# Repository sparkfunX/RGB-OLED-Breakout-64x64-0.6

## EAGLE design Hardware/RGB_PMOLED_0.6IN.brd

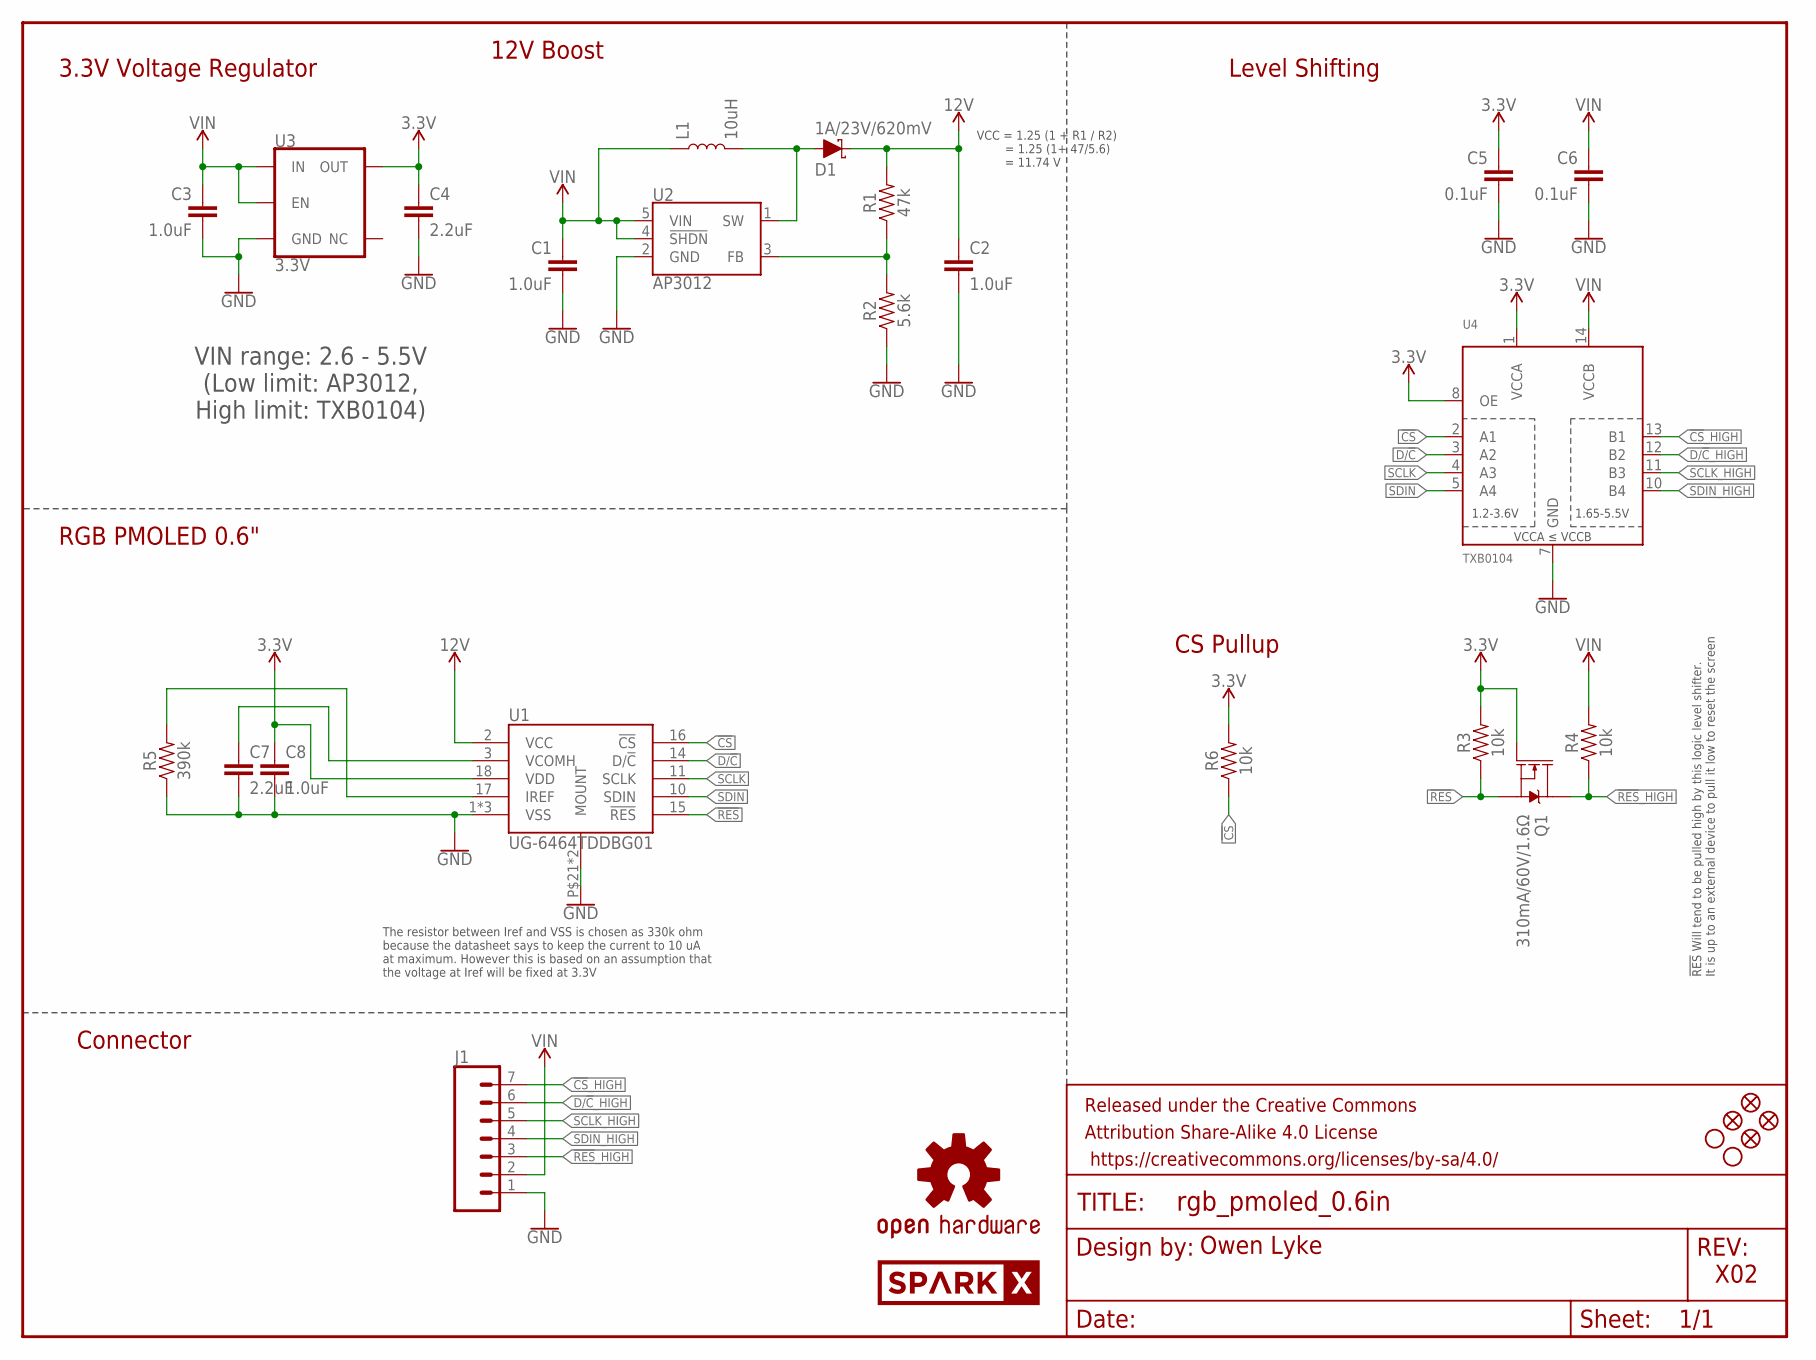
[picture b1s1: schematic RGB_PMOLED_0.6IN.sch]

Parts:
C1, C2, C3, C8: 1.0uF; 0603
C4: 2.2uF; 0603
C5, C6: 0.1uF; 0603
C7: 2.2uF; 0805
D1: 1A/23V/620mV; SOD-323
FD1, FD2, FD3, FD4: FIDUCIAL1X2; FIDUCIAL-1X2
FRAME1: FRAME-LETTER; CREATIVE_COMMONS
H1, H2: STAND-OFF
J1: CONN_07NO_SILK; 1X07_NO_SILK
L1: 10uH; INDUCTOR_4.7UH
LOGO1: SPARKX-LOGO5; SPARKX-LARGE
LOGO2: OSHW-LOGOS; OSHW-LOGO-S
Q1: 310mA/60V/1.6Ω; SOT323
R1: 47k; 0603
R2: 5.6k; 0603
R3, R4, R6: 10k; 0603
R5: 390k; 0603
U1: UG-6464TDDBG01; AMPHENOL_10051922-2010ELF
U2: AP3012; SOT23-5
U3: 3.3V; SOT23-5
U4: TXB0104; SO14

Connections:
3.3V: C4.1, C5.1, C8.1, Q1.1 (G), R3.2, R6.2, U1.18 (VDD), U3.5 (OUT), U4.1 (VCCA), U4.8 (OE)
12V: C2.1, D1.C, R1.2, U1.2 (VCC)
!CS: R6.1, U1.16 (!CS), U4.2 (A1)
!CS!_HIGH: J1.7, U4.13 (B1)
!RES: Q1.2 (S), R3.1, U1.15 (!RES)
!RES!_HIGH: J1.3, Q1.3 (D), R4.1
D/!C: U1.14 (D/!C), U4.3 (A2)
D/!C!_HIGH: J1.6, U4.12 (B2)
GND: C1.2, C2.2, C3.2, C4.2, C5.2, C6.2, C7.2, C8.2, J1.1, R2.1, R5.1, U1.1 (VSS), U1.19 (VSS), U1.20 (VSS), U1.P$21 (MOUNT), U1.P$22 (MOUNT), U2.2 (GND), U3.2 (GND), U4.7 (GND)
unnamed: D1.A, L1.P$2 (2), U2.1 (SW)
unnamed: R1.1, R2.2, U2.3 (FB)
unnamed: C7.1, U1.3 (VCOMH)
unnamed: R5.2, U1.17 (IREF)
SCLK: U1.11 (SCLK), U4.4 (A3)
SCLK_HIGH: J1.5, U4.11 (B3)
SDIN: U1.10 (SDIN), U4.5 (A4)
SDIN_HIGH: J1.4, U4.10 (B4)
VIN: C1.1, C3.1, C6.1, J1.2, L1.P$1 (1), R4.2, U2.4 (!SHDN!), U2.5 (VIN), U3.1 (IN), U3.3 (EN), U4.14 (VCCB)

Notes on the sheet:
VCC = 1.25 (1 + R1 / R2) = 1.25 (1+ 47/5.6) = 11.74 V
12V Boost
VIN range: 2.6 - 5.5V (Low limit: AP3012, High limit: TXB0104)
3.3V Voltage Regulator
Level Shifting
Owen Lyke
!RES! Will tend to be pulled high by this logic level shifter. It is up to an external device to pull it low to reset the screen
The resistor between Iref and VSS is chosen as 330k ohm because the datasheet says to keep the current to 10 uA at maximum. However this is based on an assumption that the voltage at Iref will be fixed at 3.3V
RGB PMOLED 0.6"
Connector
X02
CS Pullup

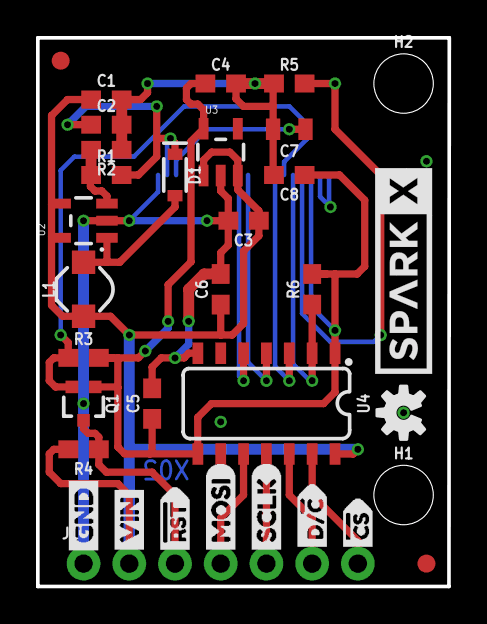
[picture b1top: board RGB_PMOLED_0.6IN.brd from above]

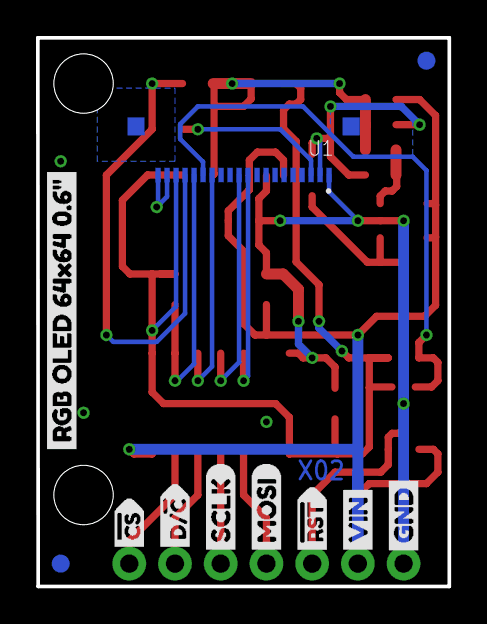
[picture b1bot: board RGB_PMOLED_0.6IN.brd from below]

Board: 2 copper layers, 22.9 x 30.5 mm, 46 parts (11 on the bottom side), 18 nets.

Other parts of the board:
U$1, U$2: VIN0
U$3, U$4: MOSI1
U$5, U$6: SCLK2
U$7, U$8: GND1
U$9, U$14: D##C5
U$10, U$11: #RST0
U$12, U$13: #CS6
U$16: RGB_OLED_64X64_0#6#7

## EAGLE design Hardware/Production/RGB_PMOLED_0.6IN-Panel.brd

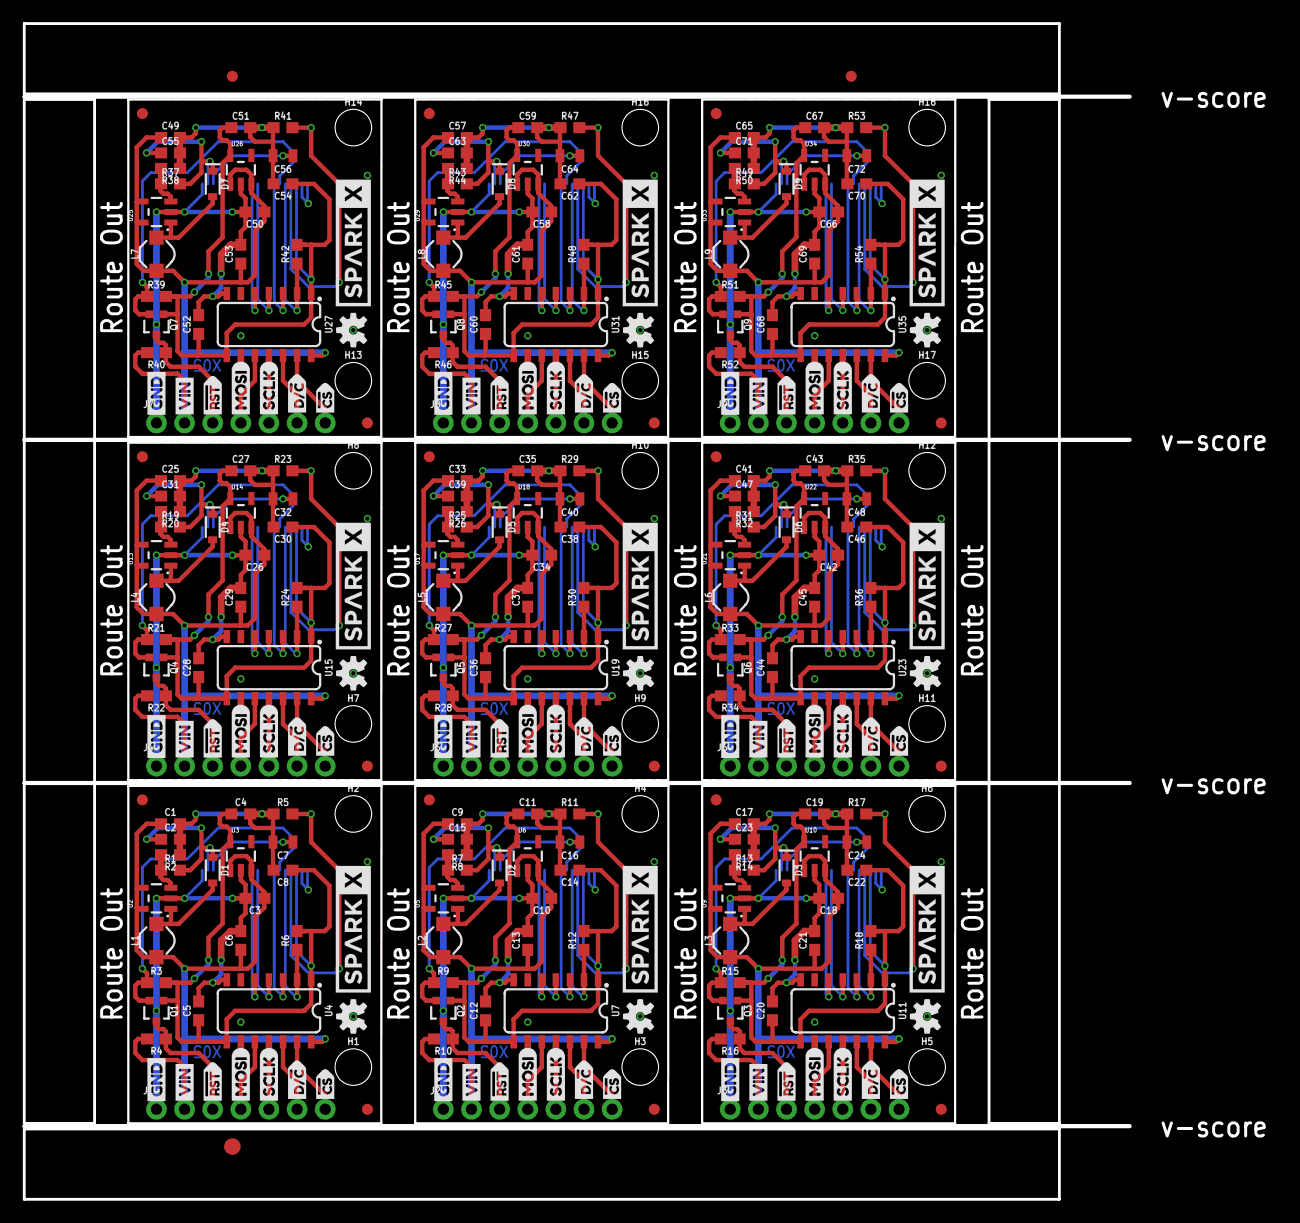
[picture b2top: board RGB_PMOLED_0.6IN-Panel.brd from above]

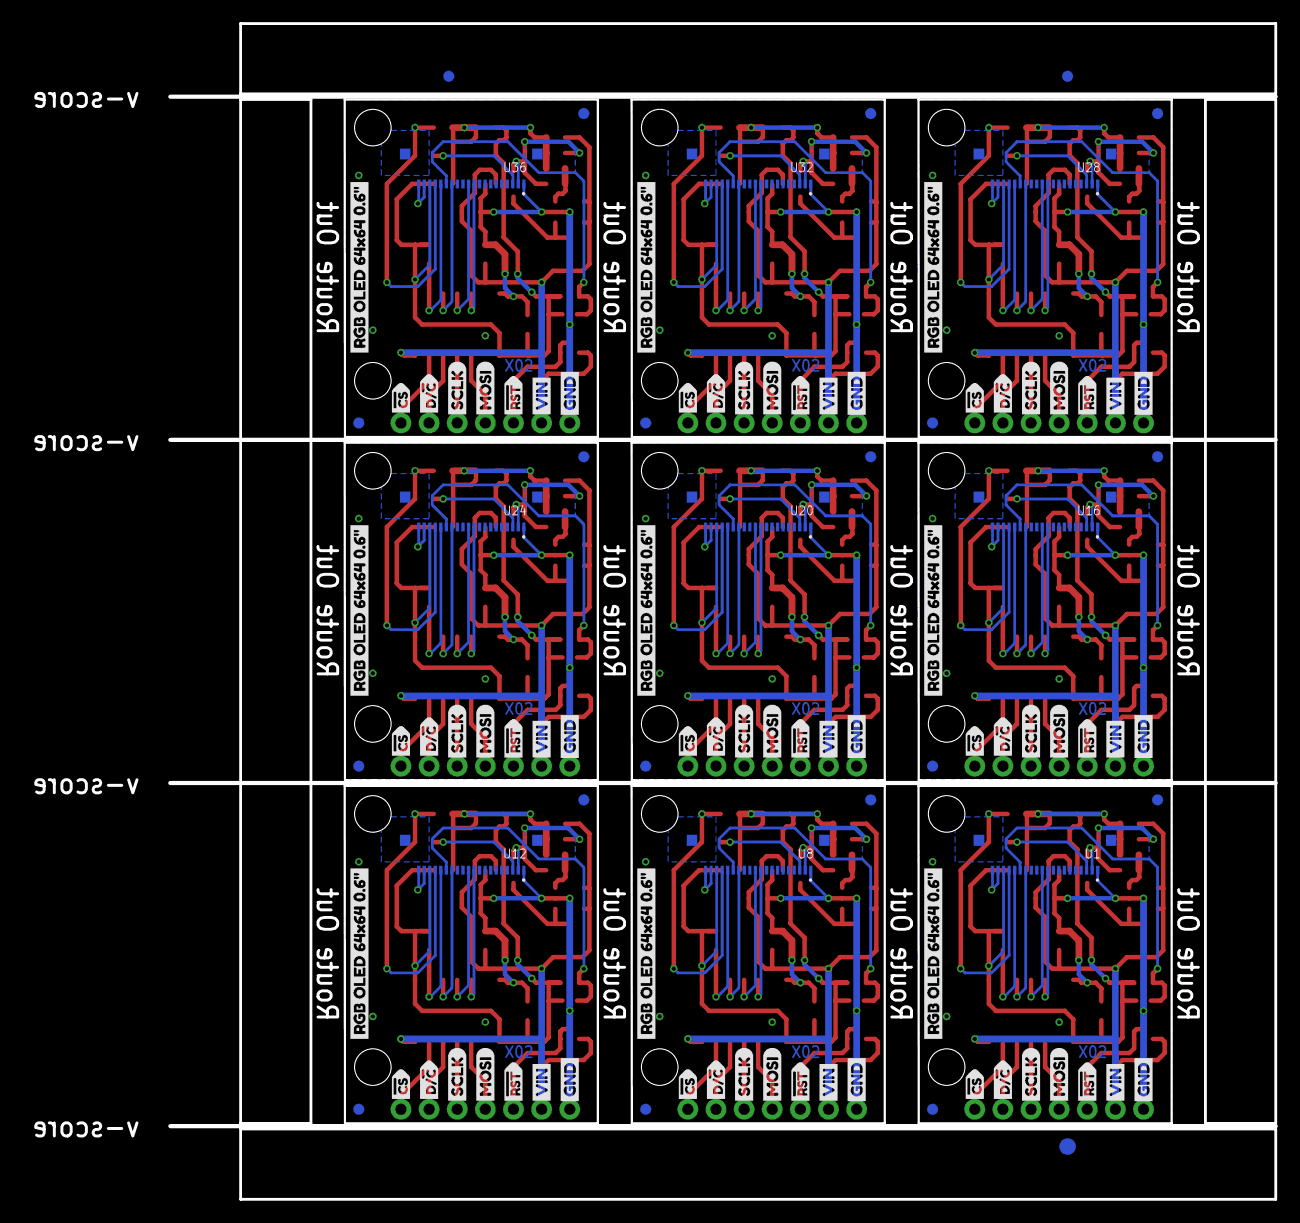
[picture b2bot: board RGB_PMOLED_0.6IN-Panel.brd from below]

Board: 2 copper layers, 113.0 x 106.0 mm, 411 parts (102 on the bottom side), 162 nets.

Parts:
C1, C2, C3, C8, C9, C10, C14, C15, C17, C18, C22, C23, C25, C26, C30, C31, C33, C34, C38, C39, C41, C42, C46, C47, C49, C50, C54, C55, C57, C58, C62, C63, C65, C66, C70, C71: 1.0uF; 0603
C4, C11, C19, C27, C35, C43, C51, C59, C67: 2.2uF; 0603
C5, C6, C12, C13, C20, C21, C28, C29, C36, C37, C44, C45, C52, C53, C60, C61, C68, C69: 0.1uF; 0603
C7, C16, C24, C32, C40, C48, C56, C64, C72: 2.2uF; 0805
D1, D2, D3, D4, D5, D6, D7, D8, D9: 1A/23V/620mV; SOD-323
E$1, E$2, E$3, E$4: FIDUCIAL-1X2
E$5, E$6: FIDUCIAL-1.5X3
FD1, FD2, FD3, FD4, FD5, FD6, FD7, FD8, FD9, FD10, FD11, FD12, FD13, FD14, FD15, FD16, FD17, FD18, FD19, FD20, FD21, FD22, FD23, FD24, FD25, FD26, FD27, FD28, FD29, FD30, FD31, FD32, FD33, FD34, FD35, FD36: FIDUCIAL1X2; FIDUCIAL-1X2
H1, H2, H3, H4, H5, H6, H7, H8, H9, H10, H11, H12, H13, H14, H15, H16, H17, H18: STAND-OFF
J1, J2, J3, J4, J5, J6, J7, J8, J9: 1X07_NO_SILK
L1, L2, L3, L4, L5, L6, L7, L8, L9: 10uH; INDUCTOR_4.7UH
LOGO1, LOGO3, LOGO5, LOGO7, LOGO9, LOGO11, LOGO13, LOGO15, LOGO17: SPARKX-LOGO5; SPARKX-LARGE
LOGO2, LOGO4, LOGO6, LOGO8, LOGO10, LOGO12, LOGO14, LOGO16, LOGO18: OSHW-LOGOS; OSHW-LOGO-S
Q1, Q2, Q3, Q4, Q5, Q6, Q7, Q8, Q9: 310mA/60V/1.6Ω; SOT323
R1, R7, R13, R19, R25, R31, R37, R43, R49: 47k; 0603
R2, R8, R14, R20, R26, R32, R38, R44, R50: 5.6k; 0603
R3, R4, R6, R9, R10, R12, R15, R16, R18, R21, R22, R24, R27, R28, R30, R33, R34, R36, R39, R40, R42, R45, R46, R48, R51, R52, R54: 10k; 0603
R5, R11, R17, R23, R29, R35, R41, R47, R53: 390k; 0603
U1, U8, U12, U16, U20, U24, U28, U32, U36: UG-6464TDDBG01; AMPHENOL_10051922-2010ELF
U2, U5, U9, U13, U17, U21, U25, U29, U33: AP3012; SOT23-5
U3, U6, U10, U14, U18, U22, U26, U30, U34: 3.3V; SOT23-5
U4, U7, U11, U15, U19, U23, U27, U31, U35: TXB0104; SO14
U$1, U$2, U$15, U$17, U$31, U$32, U$46, U$47, U$61, U$62, U$76, U$77, U$91, U$92, U$106, U$107, U$121, U$122: VIN0
U$3, U$4, U$27, U$28, U$42, U$43, U$57, U$58, U$72, U$73, U$87, U$88, U$102, U$103, U$117, U$118, U$132, U$133: MOSI1
U$5, U$6, U$29, U$30, U$44, U$45, U$59, U$60, U$74, U$75, U$89, U$90, U$104, U$105, U$119, U$120, U$134, U$135: SCLK2
U$7, U$8, U$18, U$19, U$33, U$34, U$48, U$49, U$63, U$64, U$78, U$79, U$93, U$94, U$108, U$109, U$123, U$124: GND1
U$9, U$14, U$22, U$23, U$37, U$38, U$52, U$53, U$67, U$68, U$82, U$83, U$97, U$98, U$112, U$113, U$127, U$128: D##C5
U$10, U$11, U$25, U$26, U$40, U$41, U$55, U$56, U$70, U$71, U$85, U$86, U$100, U$101, U$115, U$116, U$130, U$131: #RST0
U$12, U$13, U$20, U$21, U$35, U$36, U$50, U$51, U$65, U$66, U$80, U$81, U$95, U$96, U$110, U$111, U$125, U$126: #CS6
U$16, U$24, U$39, U$54, U$69, U$84, U$99, U$114, U$129: RGB_OLED_64X64_0#6#7

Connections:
3.3V: C4.1, C5.1, C8.1, Q1.1, R3.2, R6.2, U1.18, U3.5, U4.1, U4.8
3.3V1: C11.1, C12.1, C14.1, Q2.1, R9.2, R12.2, U6.5, U7.1, U7.8, U8.18
3.3V2: C19.1, C20.1, C22.1, Q3.1, R15.2, R18.2, U10.5, U11.1, U11.8, U12.18
3.3V3: C27.1, C28.1, C30.1, Q4.1, R21.2, R24.2, U14.5, U15.1, U15.8, U16.18
3.3V4: C35.1, C36.1, C38.1, Q5.1, R27.2, R30.2, U18.5, U19.1, U19.8, U20.18
3.3V5: C43.1, C44.1, C46.1, Q6.1, R33.2, R36.2, U22.5, U23.1, U23.8, U24.18
3.3V6: C51.1, C52.1, C54.1, Q7.1, R39.2, R42.2, U26.5, U27.1, U27.8, U28.18
3.3V7: C59.1, C60.1, C62.1, Q8.1, R45.2, R48.2, U30.5, U31.1, U31.8, U32.18
3.3V8: C67.1, C68.1, C70.1, Q9.1, R51.2, R54.2, U34.5, U35.1, U35.8, U36.18
12V: C2.1, D1.C, R1.2, U1.2
12V1: C15.1, D2.C, R7.2, U8.2
12V2: C23.1, D3.C, R13.2, U12.2
12V3: C31.1, D4.C, R19.2, U16.2
12V4: C39.1, D5.C, R25.2, U20.2
12V5: C47.1, D6.C, R31.2, U24.2
12V6: C55.1, D7.C, R37.2, U28.2
12V7: C63.1, D8.C, R43.2, U32.2
12V8: C71.1, D9.C, R49.2, U36.2
!CS: R6.1, U1.16, U4.2
!CS1: R12.1, U7.2, U8.16
!CS2: R18.1, U11.2, U12.16
!CS3: R24.1, U15.2, U16.16
!CS4: R30.1, U19.2, U20.16
!CS5: R36.1, U23.2, U24.16
!CS6: R42.1, U27.2, U28.16
!CS7: R48.1, U31.2, U32.16
!CS8: R54.1, U35.2, U36.16
!CS!_HIGH: J1.7, U4.13
!CS!_HIGH1: J2.7, U7.13
!CS!_HIGH2: J3.7, U11.13
!CS!_HIGH3: J4.7, U15.13
!CS!_HIGH4: J5.7, U19.13
!CS!_HIGH5: J6.7, U23.13
!CS!_HIGH6: J7.7, U27.13
!CS!_HIGH7: J8.7, U31.13
!CS!_HIGH8: J9.7, U35.13
!RES: Q1.2, R3.1, U1.15
!RES1: Q2.2, R9.1, U8.15
!RES2: Q3.2, R15.1, U12.15
!RES3: Q4.2, R21.1, U16.15
!RES4: Q5.2, R27.1, U20.15
!RES5: Q6.2, R33.1, U24.15
!RES6: Q7.2, R39.1, U28.15
!RES7: Q8.2, R45.1, U32.15
!RES8: Q9.2, R51.1, U36.15
!RES!_HIGH: J1.3, Q1.3, R4.1
!RES!_HIGH1: J2.3, Q2.3, R10.1
!RES!_HIGH2: J3.3, Q3.3, R16.1
!RES!_HIGH3: J4.3, Q4.3, R22.1
!RES!_HIGH4: J5.3, Q5.3, R28.1
!RES!_HIGH5: J6.3, Q6.3, R34.1
!RES!_HIGH6: J7.3, Q7.3, R40.1
!RES!_HIGH7: J8.3, Q8.3, R46.1
!RES!_HIGH8: J9.3, Q9.3, R52.1
D/!C: U1.14, U4.3
D/!C1: U7.3, U8.14
D/!C2: U11.3, U12.14
D/!C3: U15.3, U16.14
D/!C4: U19.3, U20.14
D/!C5: U23.3, U24.14
D/!C6: U27.3, U28.14
D/!C7: U31.3, U32.14
D/!C8: U35.3, U36.14
D/!C!_HIGH: J1.6, U4.12
D/!C!_HIGH1: J2.6, U7.12
D/!C!_HIGH2: J3.6, U11.12
D/!C!_HIGH3: J4.6, U15.12
D/!C!_HIGH4: J5.6, U19.12
D/!C!_HIGH5: J6.6, U23.12
D/!C!_HIGH6: J7.6, U27.12
D/!C!_HIGH7: J8.6, U31.12
D/!C!_HIGH8: J9.6, U35.12
GND: C1.2, C2.2, C3.2, C4.2, C5.2, C6.2, C7.2, C8.2, J1.1, R2.1, R5.1, U1.1, U1.19, U1.20, U1.P$21, U1.P$22, U2.2, U3.2, U4.7
GND1: C9.2, C10.2, C11.2, C12.2, C13.2, C14.2, C15.2, C16.2, J2.1, R8.1, R11.1, U5.2, U6.2, U7.7, U8.1, U8.19, U8.20, U8.P$21, U8.P$22
GND2: C17.2, C18.2, C19.2, C20.2, C21.2, C22.2, C23.2, C24.2, J3.1, R14.1, R17.1, U9.2, U10.2, U11.7, U12.1, U12.19, U12.20, U12.P$21, U12.P$22
GND3: C25.2, C26.2, C27.2, C28.2, C29.2, C30.2, C31.2, C32.2, J4.1, R20.1, R23.1, U13.2, U14.2, U15.7, U16.1, U16.19, U16.20, U16.P$21, U16.P$22
GND4: C33.2, C34.2, C35.2, C36.2, C37.2, C38.2, C39.2, C40.2, J5.1, R26.1, R29.1, U17.2, U18.2, U19.7, U20.1, U20.19, U20.20, U20.P$21, U20.P$22
GND5: C41.2, C42.2, C43.2, C44.2, C45.2, C46.2, C47.2, C48.2, J6.1, R32.1, R35.1, U21.2, U22.2, U23.7, U24.1, U24.19, U24.20, U24.P$21, U24.P$22
GND6: C49.2, C50.2, C51.2, C52.2, C53.2, C54.2, C55.2, C56.2, J7.1, R38.1, R41.1, U25.2, U26.2, U27.7, U28.1, U28.19, U28.20, U28.P$21, U28.P$22
GND7: C57.2, C58.2, C59.2, C60.2, C61.2, C62.2, C63.2, C64.2, J8.1, R44.1, R47.1, U29.2, U30.2, U31.7, U32.1, U32.19, U32.20, U32.P$21, U32.P$22
GND8: C65.2, C66.2, C67.2, C68.2, C69.2, C70.2, C71.2, C72.2, J9.1, R50.1, R53.1, U33.2, U34.2, U35.7, U36.1, U36.19, U36.20, U36.P$21, U36.P$22
unnamed: D2.A, L2.P$2, U5.1
unnamed: D1.A, L1.P$2, U2.1
unnamed: R1.1, R2.2, U2.3
unnamed: R7.1, R8.2, U5.3
unnamed: C7.1, U1.3
unnamed: R11.2, U8.17
unnamed: C16.1, U8.3
unnamed: D3.A, L3.P$2, U9.1
unnamed: R13.1, R14.2, U9.3
unnamed: R17.2, U12.17
unnamed: R5.2, U1.17
unnamed: C24.1, U12.3
unnamed: D4.A, L4.P$2, U13.1
unnamed: R19.1, R20.2, U13.3
unnamed: R23.2, U16.17
unnamed: C32.1, U16.3
unnamed: D5.A, L5.P$2, U17.1
unnamed: R25.1, R26.2, U17.3
unnamed: R29.2, U20.17
unnamed: C40.1, U20.3
unnamed: D6.A, L6.P$2, U21.1
unnamed: R31.1, R32.2, U21.3
unnamed: R35.2, U24.17
unnamed: C48.1, U24.3
unnamed: D7.A, L7.P$2, U25.1
unnamed: R37.1, R38.2, U25.3
unnamed: R41.2, U28.17
unnamed: C56.1, U28.3
unnamed: D8.A, L8.P$2, U29.1
unnamed: R43.1, R44.2, U29.3
unnamed: R47.2, U32.17
unnamed: C64.1, U32.3
unnamed: D9.A, L9.P$2, U33.1
unnamed: R49.1, R50.2, U33.3
unnamed: R53.2, U36.17
unnamed: C72.1, U36.3
SCLK: U1.11, U4.4
SCLK1: U7.4, U8.11
SCLK2: U11.4, U12.11
SCLK3: U15.4, U16.11
SCLK4: U19.4, U20.11
SCLK5: U23.4, U24.11
SCLK6: U27.4, U28.11
SCLK7: U31.4, U32.11
SCLK8: U35.4, U36.11
SCLK_HIGH: J1.5, U4.11
SCLK_HIGH1: J2.5, U7.11
SCLK_HIGH2: J3.5, U11.11
SCLK_HIGH3: J4.5, U15.11
SCLK_HIGH4: J5.5, U19.11
SCLK_HIGH5: J6.5, U23.11
SCLK_HIGH6: J7.5, U27.11
SCLK_HIGH7: J8.5, U31.11
SCLK_HIGH8: J9.5, U35.11
SDIN: U1.10, U4.5
SDIN1: U7.5, U8.10
SDIN2: U11.5, U12.10
SDIN3: U15.5, U16.10
SDIN4: U19.5, U20.10
SDIN5: U23.5, U24.10
SDIN6: U27.5, U28.10
SDIN7: U31.5, U32.10
SDIN8: U35.5, U36.10
SDIN_HIGH: J1.4, U4.10
SDIN_HIGH1: J2.4, U7.10
SDIN_HIGH2: J3.4, U11.10
SDIN_HIGH3: J4.4, U15.10
SDIN_HIGH4: J5.4, U19.10
SDIN_HIGH5: J6.4, U23.10
SDIN_HIGH6: J7.4, U27.10
SDIN_HIGH7: J8.4, U31.10
SDIN_HIGH8: J9.4, U35.10
VIN: C1.1, C3.1, C6.1, J1.2, L1.P$1, R4.2, U2.4, U2.5, U3.1, U3.3, U4.14
VIN1: C9.1, C10.1, C13.1, J2.2, L2.P$1, R10.2, U5.4, U5.5, U6.1, U6.3, U7.14
VIN2: C17.1, C18.1, C21.1, J3.2, L3.P$1, R16.2, U9.4, U9.5, U10.1, U10.3, U11.14
VIN3: C25.1, C26.1, C29.1, J4.2, L4.P$1, R22.2, U13.4, U13.5, U14.1, U14.3, U15.14
VIN4: C33.1, C34.1, C37.1, J5.2, L5.P$1, R28.2, U17.4, U17.5, U18.1, U18.3, U19.14
VIN5: C41.1, C42.1, C45.1, J6.2, L6.P$1, R34.2, U21.4, U21.5, U22.1, U22.3, U23.14
VIN6: C49.1, C50.1, C53.1, J7.2, L7.P$1, R40.2, U25.4, U25.5, U26.1, U26.3, U27.14
VIN7: C57.1, C58.1, C61.1, J8.2, L8.P$1, R46.2, U29.4, U29.5, U30.1, U30.3, U31.14
VIN8: C65.1, C66.1, C69.1, J9.2, L9.P$1, R52.2, U33.4, U33.5, U34.1, U34.3, U35.14

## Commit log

2018-06-12 Intemediate commit
2018-06-12 First revision
2018-06-13 Updated and added datasheets
2018-06-13 Panelized and gerberified
2018-06-15 Needed
2018-07-13 Revision 2 of board using a connector
2018-07-13 Fixed clearance of 4-40 screw
2018-07-18 Cleaned up documentation

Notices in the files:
parts and their libraries:
SparkFun-Capacitors: Licensing: Creative Commons ShareAlike 4.0 International - https://creativecommons.org/licenses/by-sa/4.0
SparkFun-Aesthetics: Released under the Creative Commons Attribution Share-Alike 4.0 License
SparkFun-Aesthetics: https://creativecommons.org/licenses/by-sa/4.0
